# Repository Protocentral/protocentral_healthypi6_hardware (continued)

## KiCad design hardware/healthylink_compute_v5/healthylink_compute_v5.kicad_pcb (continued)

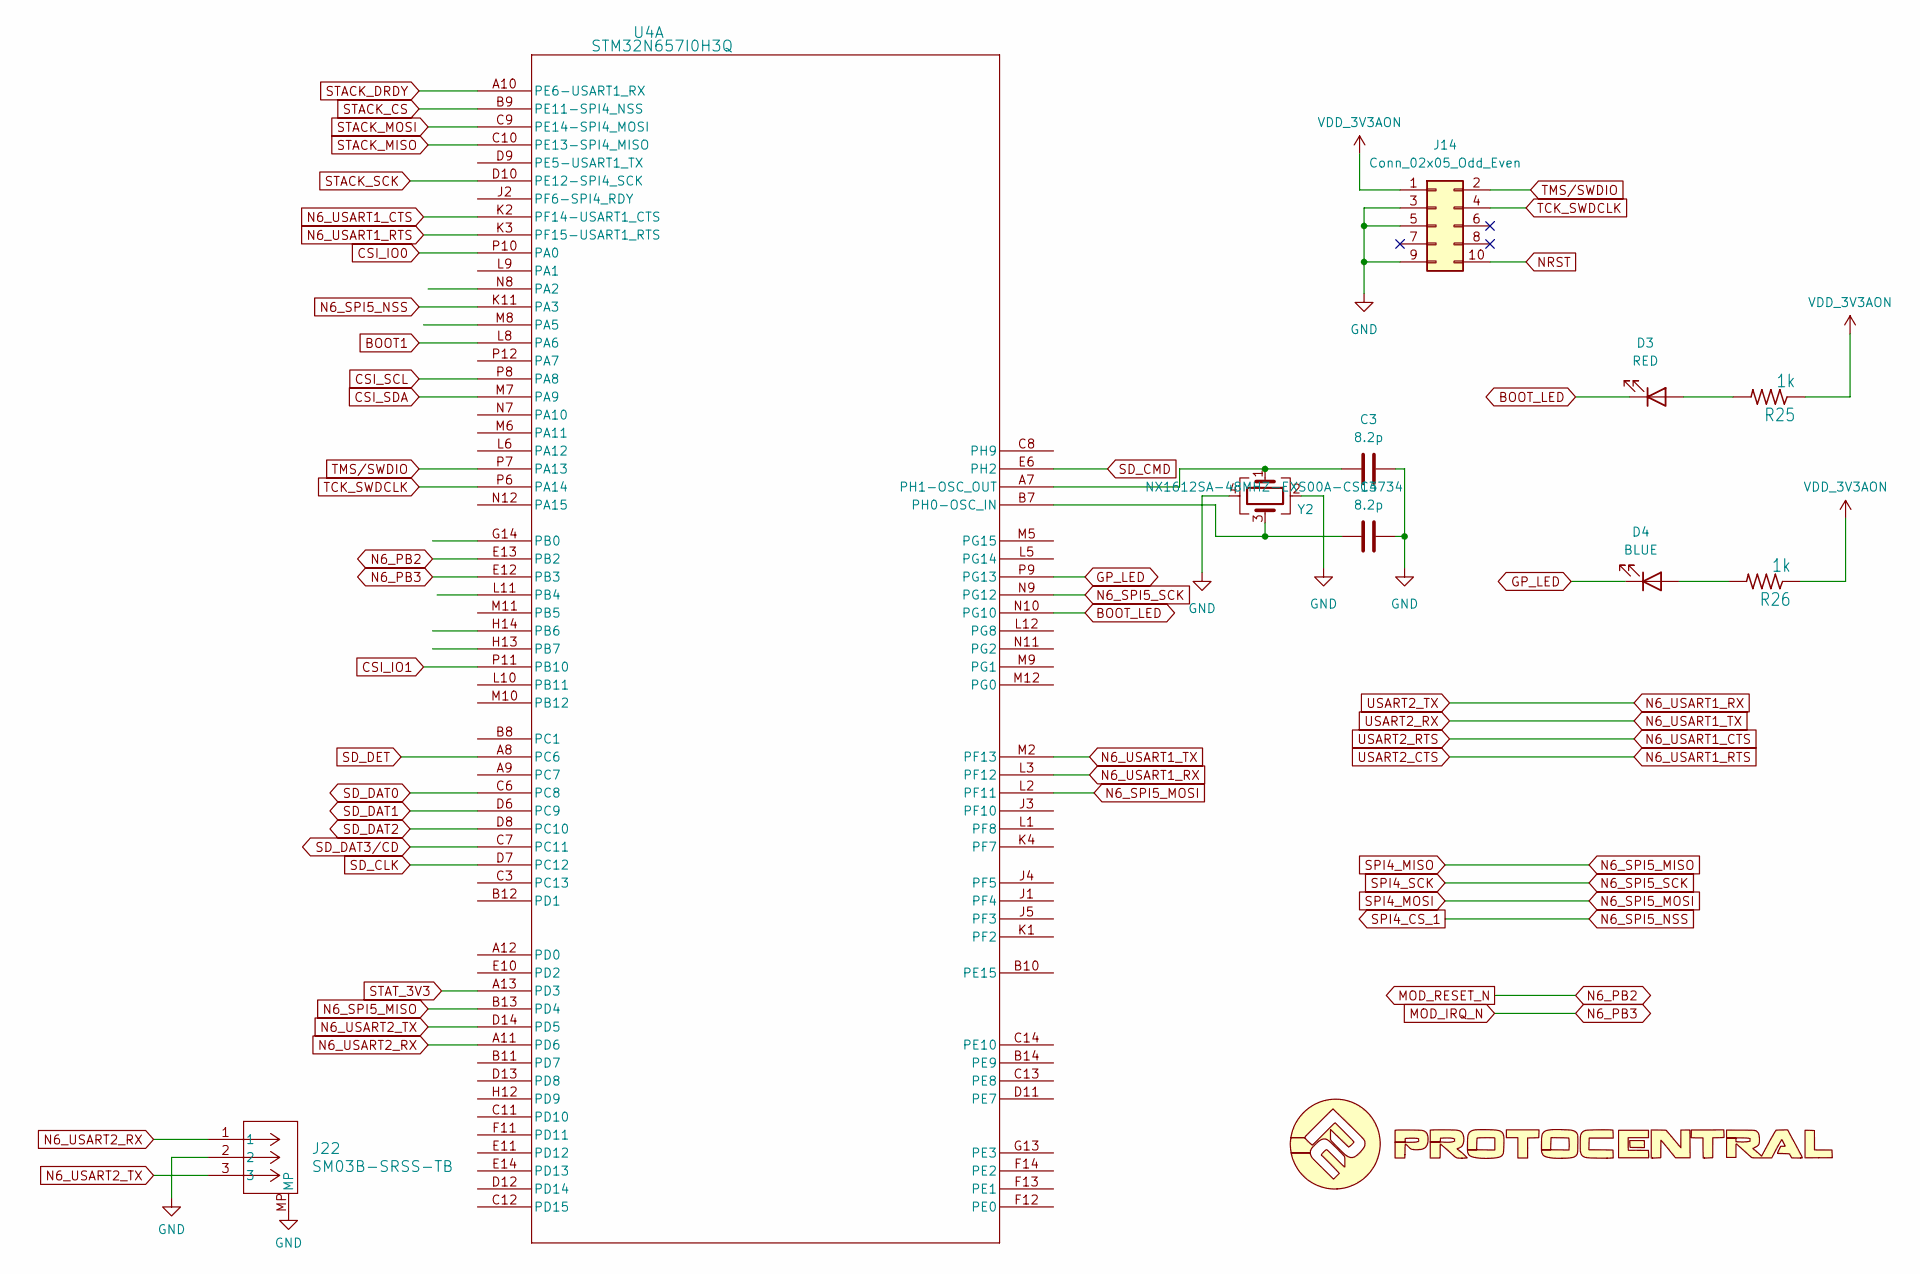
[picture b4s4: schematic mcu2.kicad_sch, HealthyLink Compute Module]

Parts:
C3, C4: 8.2p; C_0402_1005Metric
D3: RED; LED_0603_1608Metric
D4: BLUE; LED_0603_1608Metric
J14: Conn_02x05_Odd_Even; PinHeader_2x05_P1.27mm_Vertical_SMD
J22: SM03B-SRSS-TB; JST_SH_SM03B-SRSS-TB_1x03-1MP_P1.00mm_Horizontal
R25, R26: 1k; R_0402_1005Metric
U4: STM32N657I0H3Q; VFBGA178_12X12_STM
U21: LOGO
Y2: NX1612SA-48MHZ-EXS00A-CS13734; Crystal_1612

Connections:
BOOT1: U4.L8 (PA6); also elsewhere on the board
BOOT_LED: D3.1 (K), U4.N10 (PG10)
CSI_IO0: U4.P10 (PA0); also elsewhere on the board
CSI_IO1: U4.P11 (PB10); also elsewhere on the board
CSI_SCL: U4.P8 (PA8); also elsewhere on the board
CSI_SDA: U4.M7 (PA9); also elsewhere on the board
GND: C3.2, C4.2, J14.3, J14.5, J14.9, J22.2, J22.MP, Y2.2, Y2.4; also elsewhere on the board
GP_LED: D4.1 (K), U4.P9 (PG13)
MOD_IRQ_N: U4.E12 (PB3); also elsewhere on the board
MOD_RESET_N: U4.E13 (PB2); also elsewhere on the board
N6_SPI5_MISO: U4.B13 (PD4); also elsewhere on the board
N6_SPI5_MOSI: U4.L2 (PF11); also elsewhere on the board
N6_SPI5_NSS: U4.K11 (PA3); also elsewhere on the board
N6_SPI5_SCK: U4.N9 (PG12); also elsewhere on the board
N6_USART1_CTS: U4.K2 (PF14-USART1_CTS); also elsewhere on the board
N6_USART1_RTS: U4.K3 (PF15-USART1_RTS); also elsewhere on the board
N6_USART1_RX: U4.L3 (PF12); also elsewhere on the board
N6_USART1_TX: U4.M2 (PF13); also elsewhere on the board
N6_USART2_RX: J22.1, U4.A11 (PD6)
N6_USART2_TX: J22.3, U4.D14 (PD5)
NRST: J14.10; also elsewhere on the board
unnamed: D3.2 (A), R25.2
unnamed: D4.2 (A), R26.2
unnamed: C4.1, U4.B7 (PH0-OSC_IN), Y2.3
unnamed: C3.1, U4.A7 (PH1-OSC_OUT), Y2.1
SD_CLK: U4.D7 (PC12); also elsewhere on the board
SD_CMD: U4.E6 (PH2); also elsewhere on the board
SD_DAT0: U4.C6 (PC8); also elsewhere on the board
SD_DAT1: U4.D6 (PC9); also elsewhere on the board
SD_DAT2: U4.D8 (PC10); also elsewhere on the board
SD_DAT3/CD: U4.C7 (PC11); also elsewhere on the board
SD_DET: U4.A8 (PC6); also elsewhere on the board
STACK_CS: U4.B9 (PE11-SPI4_NSS); also elsewhere on the board
STACK_DRDY: U4.A10 (PE6-USART1_RX); also elsewhere on the board
STACK_MISO: U4.C10 (PE13-SPI4_MISO); also elsewhere on the board
STACK_MOSI: U4.C9 (PE14-SPI4_MOSI); also elsewhere on the board
STACK_SCK: U4.D10 (PE12-SPI4_SCK); also elsewhere on the board
STAT_3V3: U4.A13 (PD3); also elsewhere on the board
TCK_SWDCLK: J14.4, U4.P6 (PA14)
TMS/SWDIO: J14.2, U4.P7 (PA13)
VDD_3V3AON: J14.1, R25.1, R26.1; also elsewhere on the board

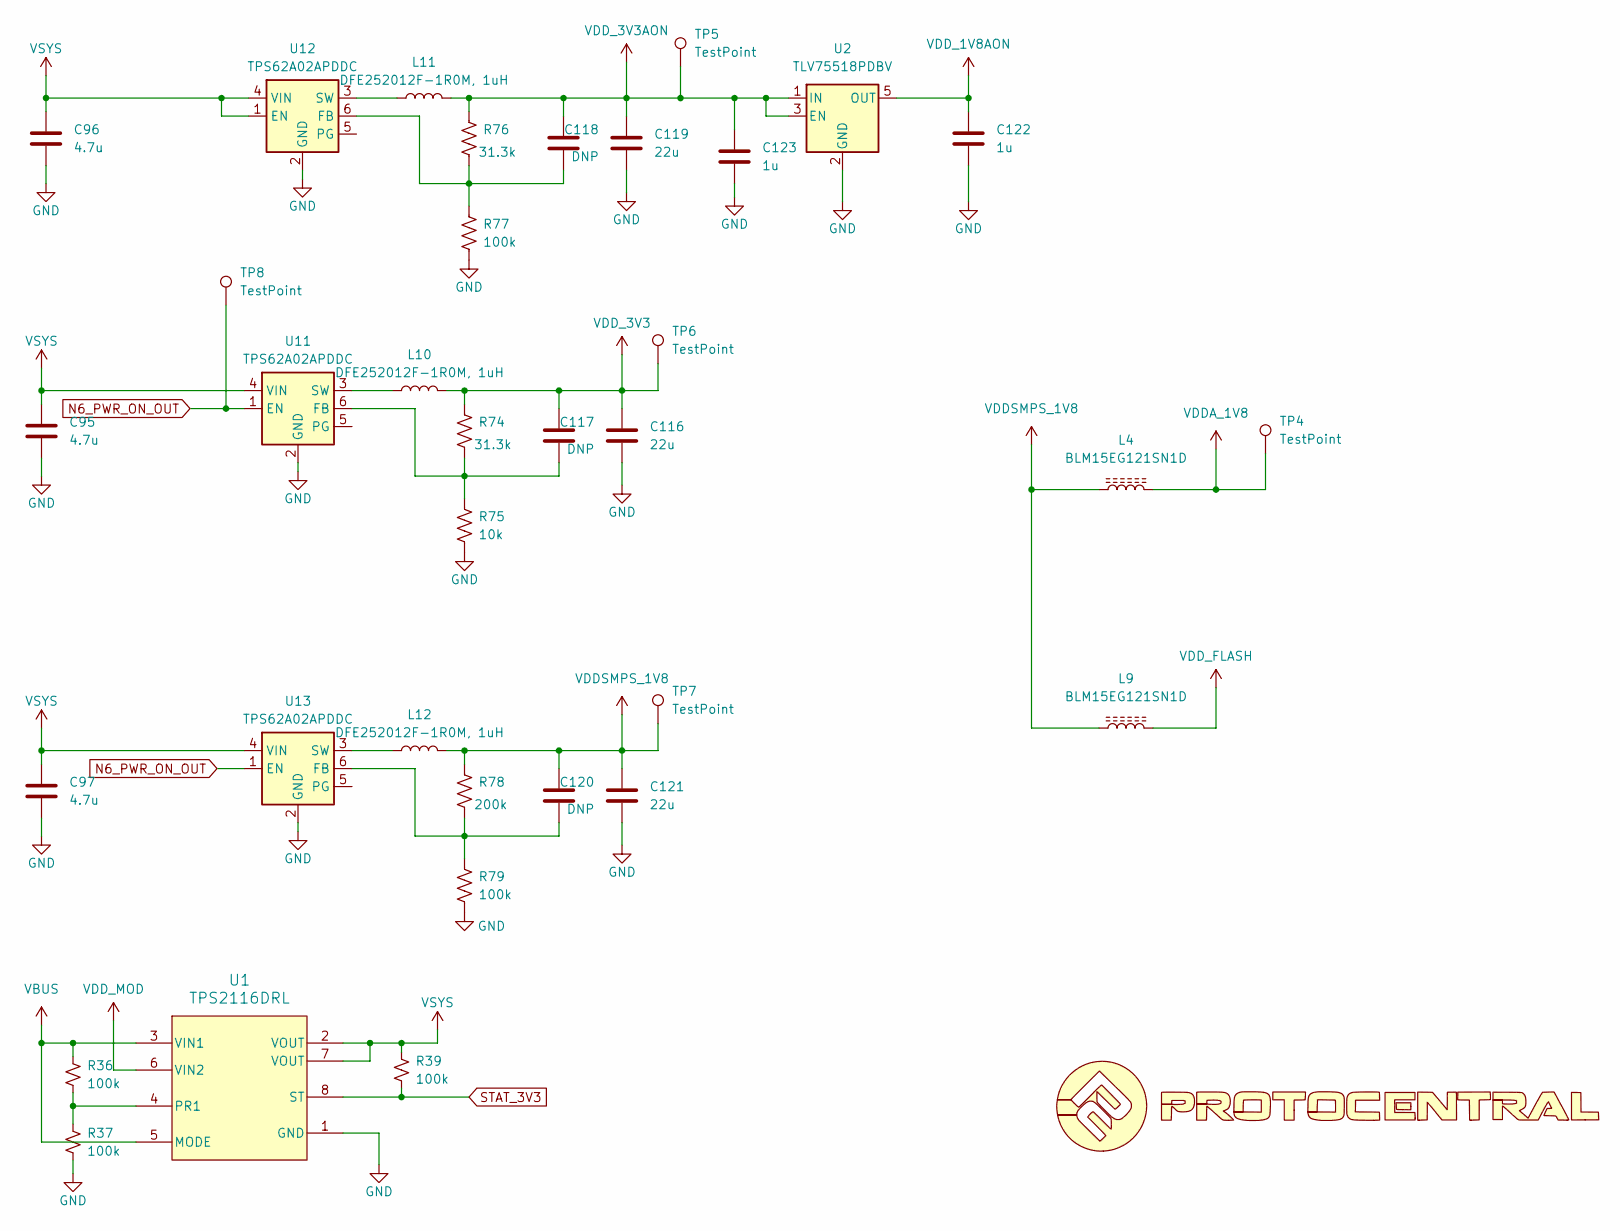
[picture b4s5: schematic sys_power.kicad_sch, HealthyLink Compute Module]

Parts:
C95, C96, C97: 4.7u; C_0805_2012Metric
C116, C119, C121: 22u; C_0805_2012Metric
C117, C118, C120: DNP; C_0402_1005Metric
C122, C123: 1u; C_0805_2012Metric
L4, L9: BLM15EG121SN1D; L_0402_1005Metric
L10, L11, L12: DFE252012F-1R0M, 1uH; L_1008_2520Metric
R36, R37, R39, R77, R79: 100k; R_0402_1005Metric
R74, R76: 31.3k; R_0402_1005Metric
R75: 10k; R_0402_1005Metric
R78: 200k; R_0402_1005Metric
TP4, TP5, TP6, TP7, TP8: TestPoint; TestPoint_Pad_D1.0mm
U1: TPS2116DRL; DRL0008A-MFG
U2: TLV75518PDBV; SOT-23-5
U11, U12, U13: TPS62A02APDDC; SOT-23-6
U19: LOGO

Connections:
GND: C95.2, C96.2, C97.2, C116.2, C119.2, C121.2, C122.2, C123.2, R37.2, R75.1, R77.1, R79.1, U1.1 (GND), U2.2 (GND), U11.2 (GND), U12.2 (GND), U13.2 (GND); also elsewhere on the board
N6_PWR_ON_OUT: TP8.1 (1_1), U11.1 (EN), U13.1 (EN); also elsewhere on the board
unnamed: R36.2, R37.1, U1.4 (PR1)
unnamed: C117.1, R74.1, R75.2, U11.6 (FB)
unnamed: L10.1, U11.3 (SW)
unnamed: C118.1, R76.1, R77.2, U12.6 (FB)
unnamed: L11.1, U12.3 (SW)
unnamed: C120.1, R78.1, R79.2, U13.6 (FB)
unnamed: L12.1, U13.3 (SW)
STAT_3V3: R39.2, U1.8 (ST); also elsewhere on the board
VBUS: R36.1, U1.3 (VIN1), U1.5 (MODE); also elsewhere on the board
VDDA_1V8: L4.2, TP4.1 (1_1); also elsewhere on the board
VDDSMPS_1V8: C120.2, C121.1, L4.1, L9.1, L12.2, R78.2, TP7.1 (1_1); also elsewhere on the board
VDD_1V8AON: C122.1, U2.5 (OUT); also elsewhere on the board
VDD_3V3: C116.1, C117.2, L10.2, R74.2, TP6.1 (1_1); also elsewhere on the board
VDD_3V3AON: C118.2, C119.1, C123.1, L11.2, R76.2, TP5.1 (1_1), U2.1 (IN), U2.3 (EN); also elsewhere on the board
VDD_FLASH: L9.2; also elsewhere on the board
VDD_MOD: U1.6 (VIN2); also elsewhere on the board
VSYS: C95.1, C96.1, C97.1, R39.1, U1.2 (VOUT), U1.7 (VOUT), U11.4 (VIN), U12.1 (EN), U12.4 (VIN), U13.4 (VIN)

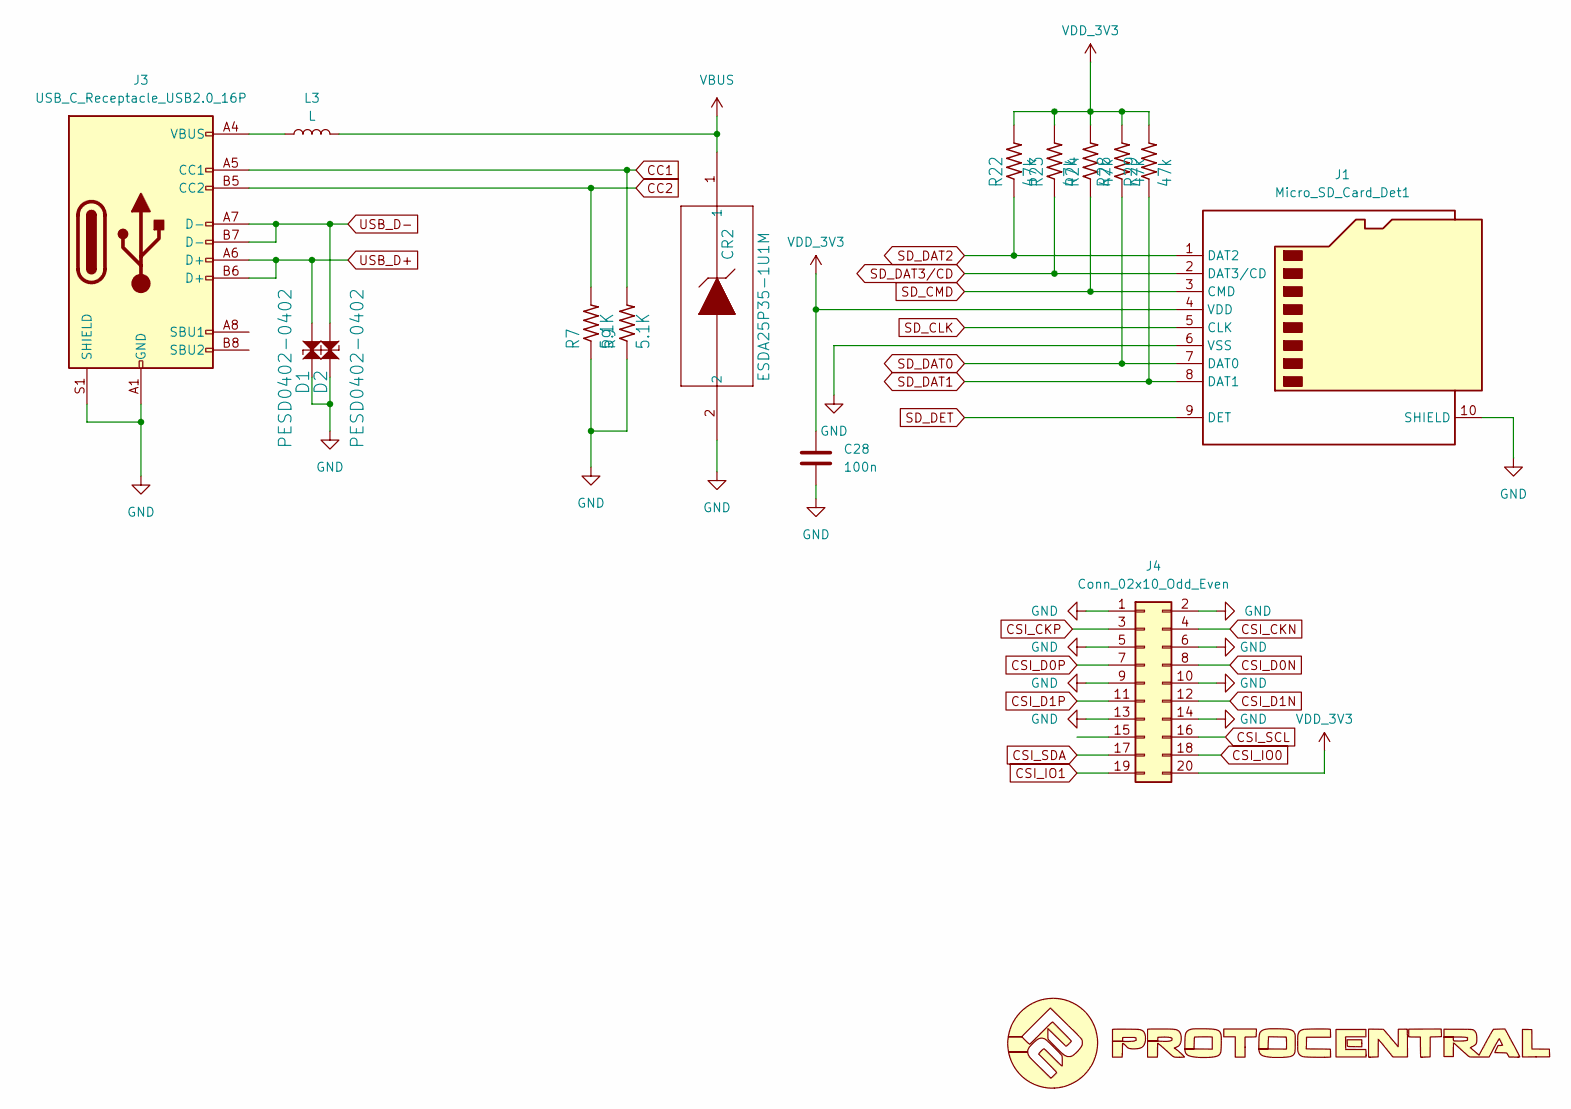
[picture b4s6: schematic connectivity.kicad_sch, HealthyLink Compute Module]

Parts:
C28: 100n; C_0402_1005Metric
CR2: ESDA25P35-1U1M; ST_QFN-2L_1.6x1.0mm
D1, D2: PESD0402-0402; D_SOD-882D
J1: Micro_SD_Card_Det1; GCT_MEM2052-00-195-00-A_REVA
J3: USB_C_Receptacle_USB2.0_16P; USB_C_Receptacle_GCT_USB4105-xx-A_16P_TopMnt_Horizontal
J4: Conn_02x10_Odd_Even; PinHeader_2x10_P1.27mm_Vertical_SMD
L3: L; L_1008_2520Metric
R7, R9: 5.1K; R_0402_1005Metric
R22, R23, R24, R28, R29: 47k; R_0402_1005Metric
U20: LOGO

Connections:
CC1: J3.A5 (CC1), R9.2
CC2: J3.B5 (CC2), R7.2
CSI_CKN: J4.4; also elsewhere on the board
CSI_CKP: J4.3; also elsewhere on the board
CSI_D0N: J4.8; also elsewhere on the board
CSI_D0P: J4.7; also elsewhere on the board
CSI_D1N: J4.12; also elsewhere on the board
CSI_D1P: J4.11; also elsewhere on the board
CSI_IO0: J4.18; also elsewhere on the board
CSI_IO1: J4.19; also elsewhere on the board
CSI_SCL: J4.16; also elsewhere on the board
CSI_SDA: J4.17; also elsewhere on the board
GND: C28.1, CR2.2, D1.1, D2.1, J1.6 (VSS), J1.10 (SHIELD), J3.A1 (GND), J3.A12 (GND), J3.B1 (GND), J3.B12 (GND), J3.S1 (SHIELD), J4.1, J4.2, J4.5, J4.6, J4.9, J4.10, J4.13, J4.14, R7.1, R9.1; also elsewhere on the board
unnamed: J3.A4 (VBUS), J3.A9 (VBUS), J3.B4 (VBUS), J3.B9 (VBUS), L3.1
SD_CLK: J1.5 (CLK); also elsewhere on the board
SD_CMD: J1.3 (CMD), R24.1; also elsewhere on the board
SD_DAT0: J1.7 (DAT0), R28.1; also elsewhere on the board
SD_DAT1: J1.8 (DAT1), R29.1; also elsewhere on the board
SD_DAT2: J1.1 (DAT2), R22.1; also elsewhere on the board
SD_DAT3/CD: J1.2 (DAT3/CD), R23.1; also elsewhere on the board
SD_DET: J1.9 (DET); also elsewhere on the board
USB_D+: D1.2, J3.A6 (D+), J3.B6 (D+); also elsewhere on the board
USB_D-: D2.2, J3.A7 (D-), J3.B7 (D-); also elsewhere on the board
VBUS: CR2.1, L3.2; also elsewhere on the board
VDD_3V3: C28.2, J1.4 (VDD), J4.20, R22.2, R23.2, R24.2, R28.2, R29.2; also elsewhere on the board

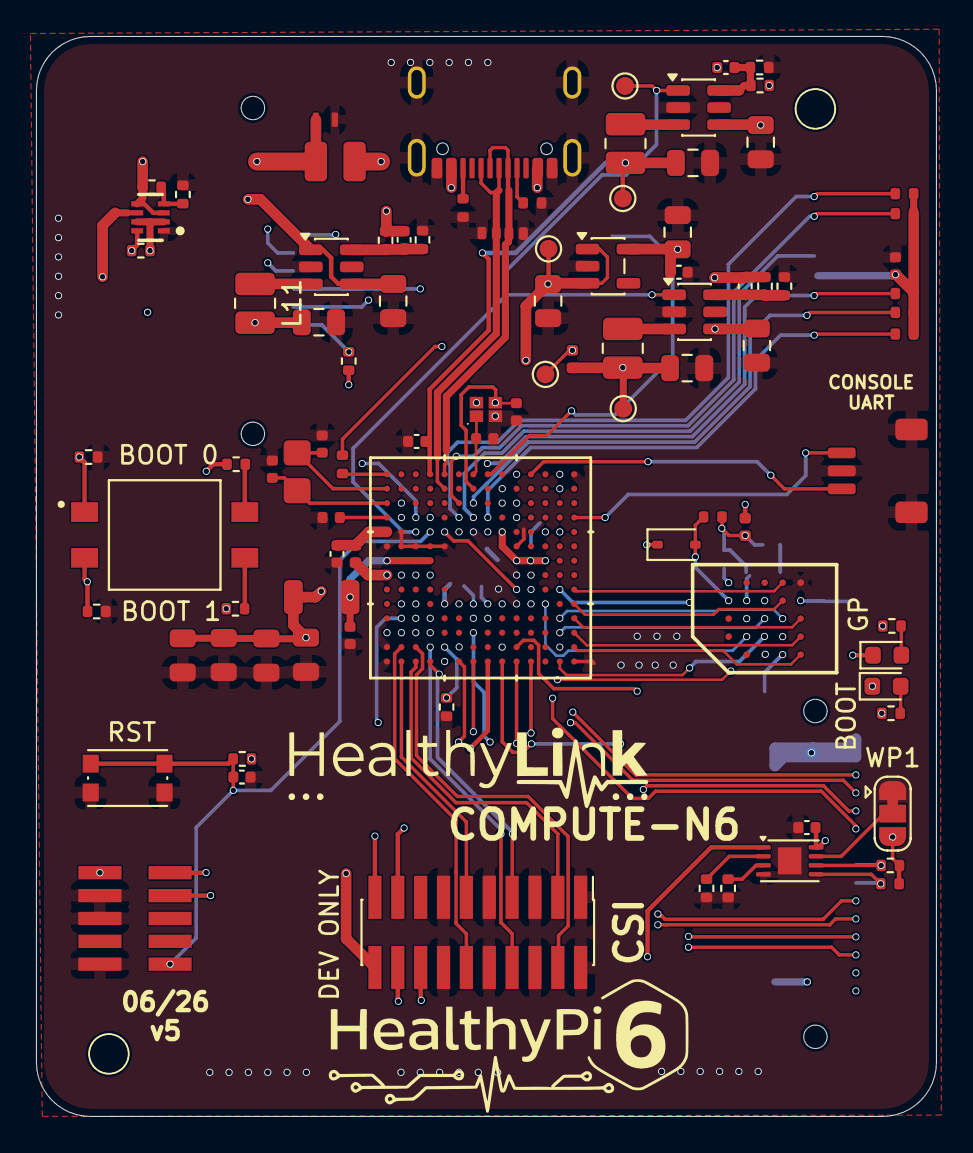
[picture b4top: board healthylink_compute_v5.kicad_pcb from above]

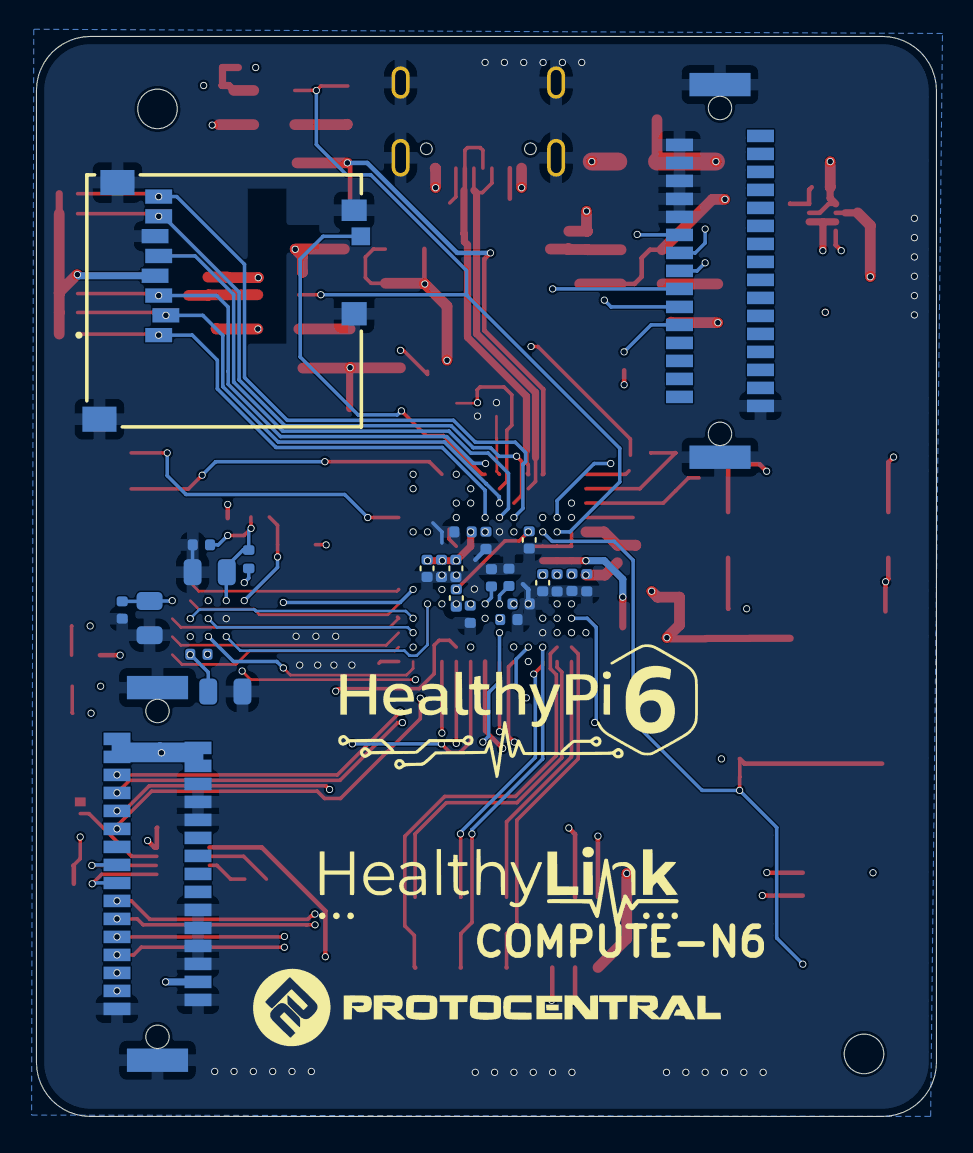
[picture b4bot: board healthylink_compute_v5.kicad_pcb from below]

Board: 6 copper layers, 50.0 x 60.0 mm, 119 parts (24 on the bottom side), 100 nets.
